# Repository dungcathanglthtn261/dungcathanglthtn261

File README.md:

# Smart Irrigation System – Bài tập lớn LTHTN (HK261)

Thiết bị đo độ ẩm đất và tự động tưới cây, dùng **STM32F103C8 (Blue Pill)** + FreeRTOS.
Đồ án môn **Lập trình Hệ thống nhúng** – HCMUT.

Nhóm: Dũng · Ca · Thắng

## Chức năng

- Đọc độ ẩm đất qua ADC mỗi 1000 ms, quy đổi 0–100 % (độ phân giải 1 %).
- **AUTO**: bật bơm khi độ ẩm < ngưỡng (setpoint), tắt khi đạt ngưỡng.
- **MANUAL**: bật/tắt bơm bằng nút PUMP, không phụ thuộc cảm biến.
- LCD 16x2 hiển thị độ ẩm, ngưỡng, chế độ, trạng thái bơm.
- Gửi dữ liệu lên PC qua UART, ví dụ: `SOIL: 45% | SET: 60% | MODE: AUTO | PUMP: ON`.

## Cấu trúc repo

```
docs/                Đề tài, yêu cầu chung, bảng phân công, sơ đồ khối
hardware/kicad/      Project KiCad: schematic, PCB 10x10 cm, thư viện symbol/footprint riêng
hardware/images/     Ảnh xem nhanh schematic và PCB
firmware/            Code STM32 + FreeRTOS: app/ (task, logic), middleware/ (soil_sensor, lcd16x02, relay_pump)
docs/test/           Kịch bản kiểm thử
docs/flowcharts/     Lưu đồ giải thuật (mermaid + png)
simulation/mokxi/    diagram.json (định dạng Wokwi) + sketch.ino để mô phỏng trên Mokxi/Wokwi
```

## Gán chân (Blue Pill)

| Khối | Chân | Ghi chú |
|---|---|---|
| Cảm biến độ ẩm | PA0 (ADC1_IN0) | Cấp 3V3, tụ lọc 100 nF |
| UART → PC | PA2 TX, PA3 RX (USART2) | 115200 8N1, nối chéo TX/RX với USB-UART |
| Relay | PA4 | Module relay 5V, kích mức **thấp** |
| LCD 16x2 (4-bit) | RS PB0, E PB1, D4–D7 PB10–PB13 | RW nối GND, biến trở 10k chỉnh tương phản, 220 Ω đèn nền |
| Nút MODE / UP / DOWN / PUMP | PB5 / PB6 / PB7 / PB8 | Pull-up nội, nhấn = LOW, tụ 100 nF chống dội |
| Nạp / debug | Header SWD trên Blue Pill | PA13/PA14 không có trên 2 hàng chân bên hông |

## Phần cứng (KiCad)

Mở `hardware/kicad/smart_irrigation.kicad_pro` bằng KiCad 9/10. Thư viện symbol và footprint
riêng đã khai báo trong `sym-lib-table` / `fp-lib-table` của project (đường dẫn `${KIPRJMOD}`).

- Board 100 × 100 mm, 2 lớp, mặt dưới phủ đồng GND, 4 lỗ M3.
- Blue Pill cắm qua 2 hàng **header cái 1x20** (hàng cách nhau 15.24 mm), không hàn trực tiếp.
- LCD cắm qua header cái 16 chân; relay module gắn ngoài (J7 điều khiển, J8 tiếp điểm COM/NO).
- Dây tín hiệu 0.5 mm, dây nguồn 1.0 mm, khoảng cách 0.3 mm.
- ERC: 0 lỗi. DRC: 0 lỗi, còn 4 cảnh báo silkscreen của footprint nút nhấn chuẩn KiCad.

**Cần kiểm tra trước khi đặt mạch:** in PCB tỉ lệ 1:1 để ướm Blue Pill thật (pinout, khoảng
cách hàng, chiều USB) và hướng lỗ luồn dây của cầu đấu vít.

## Mô phỏng

Ubuntu không chạy được Proteus, nhóm dùng **Mokxi** (mô phỏng trên trình duyệt):

- `simulation/mokxi/mokxi_project.json`: project định dạng Mokxi (`mokxi-ai/1`), đã qua
  `validate_project` của Mokxi, 0 lỗi. Dùng cảm biến độ ẩm điện dung, máy bơm mini chạy pin 4xAA
  qua relay kích mức thấp, diode chống dòng ngược. Serial Monitor in gói tin UART.
- **Project Mokxi (layout gọn, chạy được):** https://app.mokxi.com/p/RN2hMLpKIqXbyVL_  
  Vị trí/đường dây nằm trong `diagram_mokxi_native.json`; code Mokxi: `sketch_mokxi.ino`.
- `simulation/mokxi/diagram.json` + `sketch.ino`: bản định dạng Wokwi (biến trở thay cảm biến,
  LED thay máy bơm).

Hằng số `ADC_DRY` / `ADC_WET` trong code phải hiệu chuẩn lại trên mạch thật.

## Việc tiếp theo

- [ ] Firmware STM32CubeIDE + FreeRTOS (5 task: SensorRead, ButtonProcess, Control, Display, UART_Tx)
- [ ] Xuất Gerber, làm mạch, hàn linh kiện
- [ ] Hiệu chuẩn cảm biến, chạy kịch bản kiểm thử
- [ ] Báo cáo

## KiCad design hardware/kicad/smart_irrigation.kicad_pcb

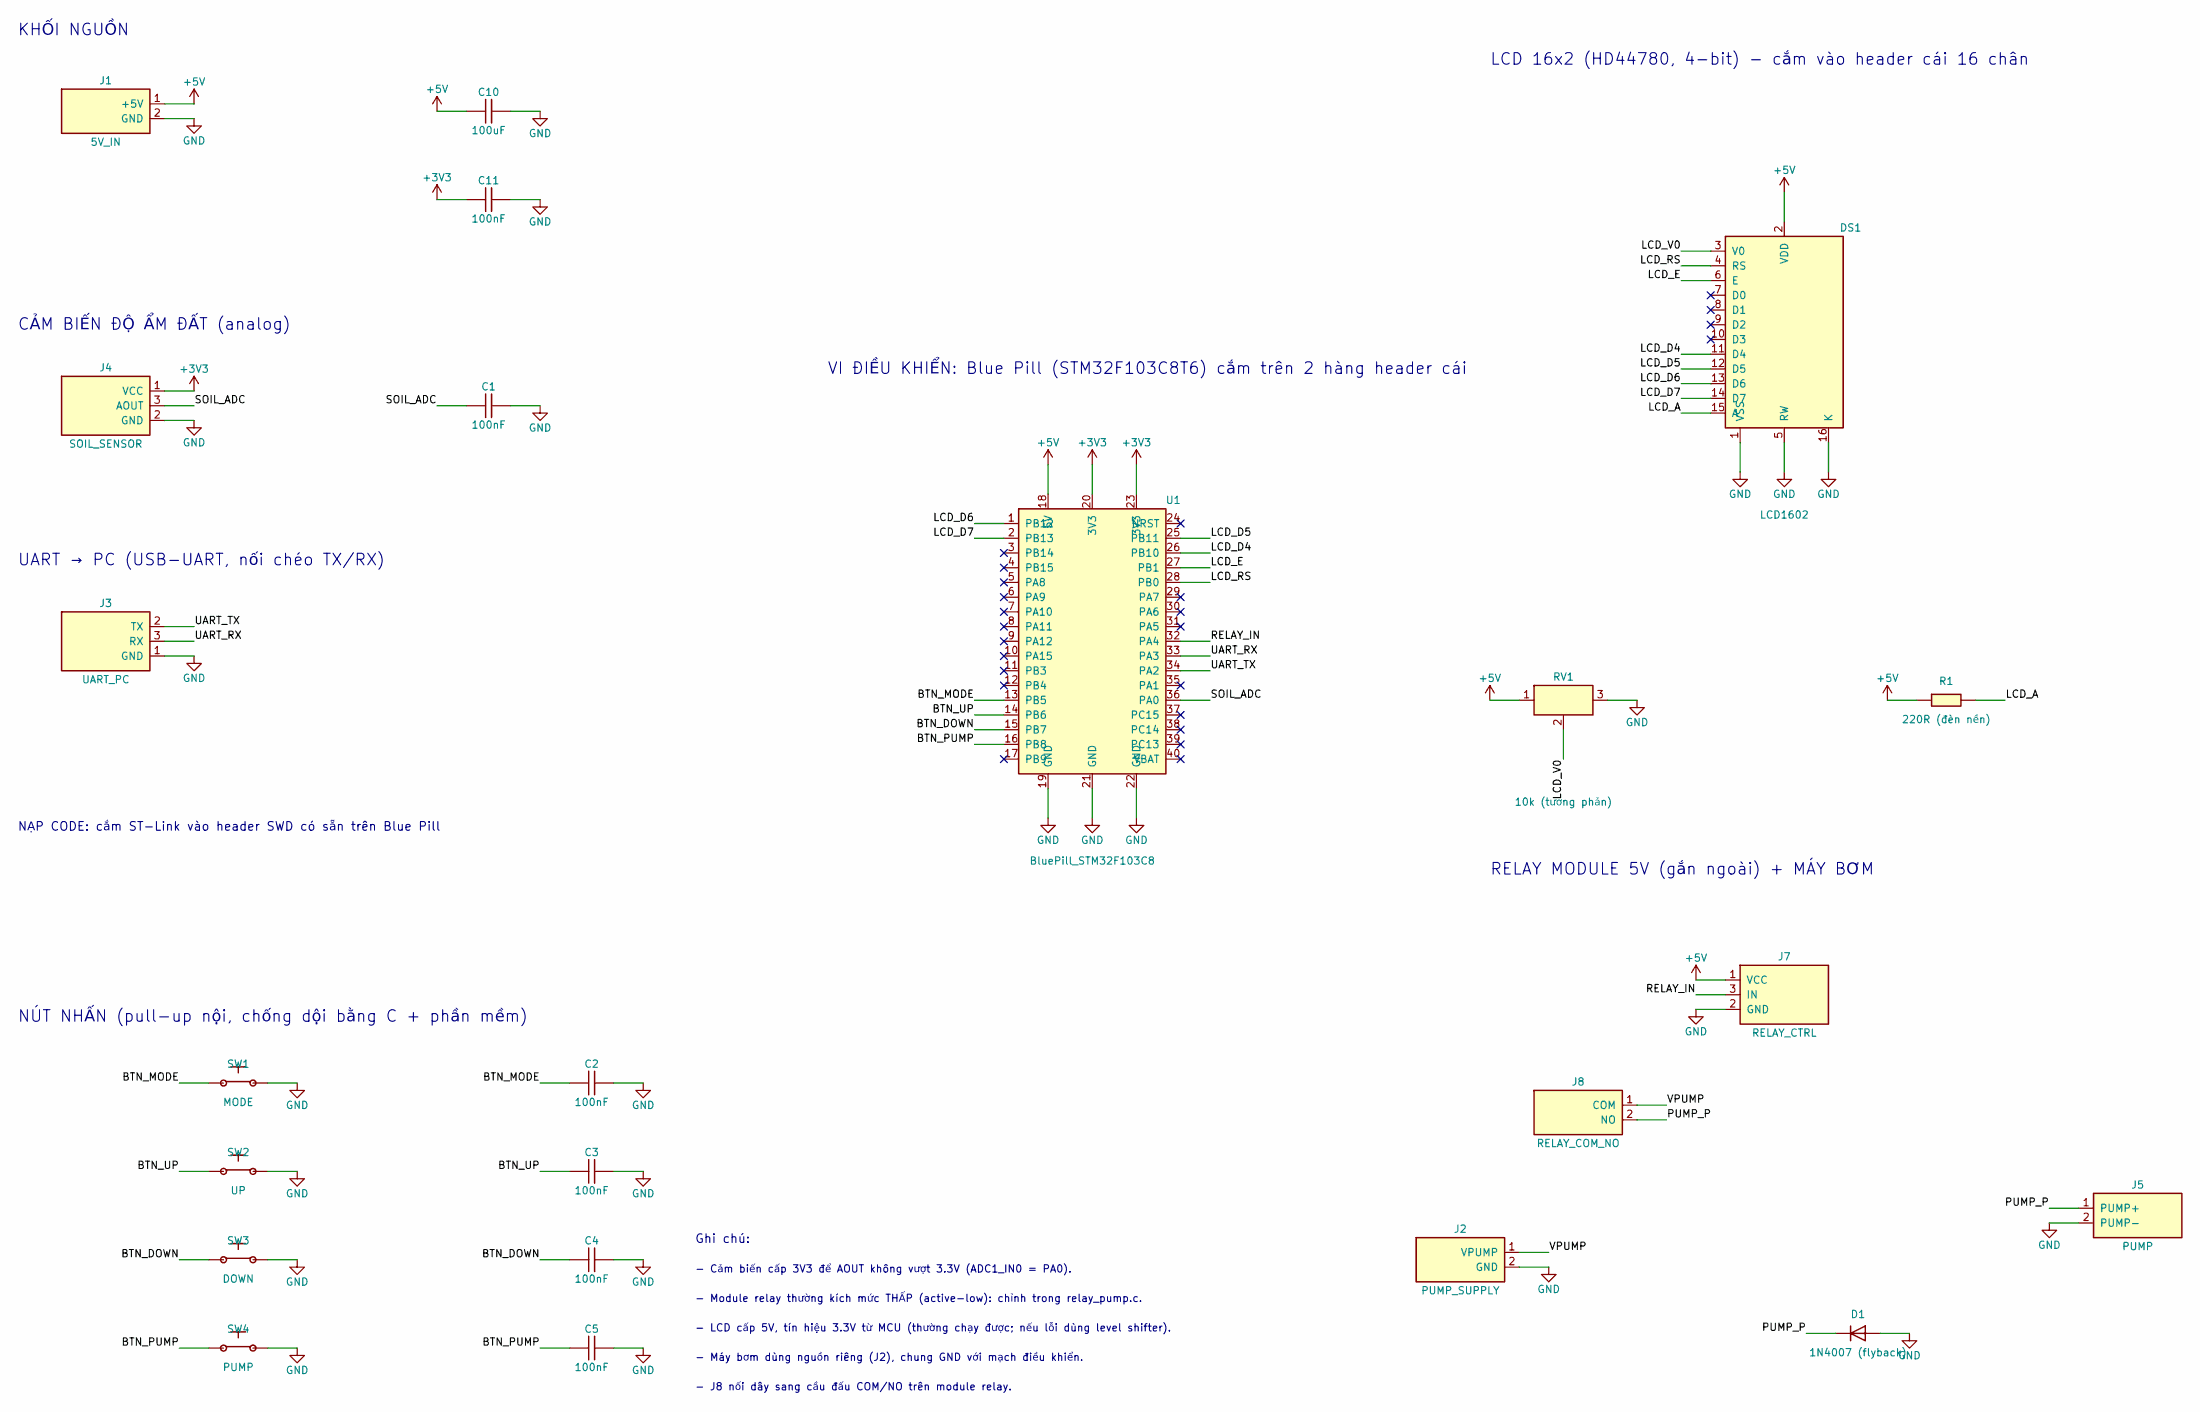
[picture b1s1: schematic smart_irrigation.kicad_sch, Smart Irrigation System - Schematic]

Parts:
C1, C2, C3, C4, C5, C11: 100nF; C_Disc_D5.0mm_W2.5mm_P5.00mm
C10: 100uF; CP_Radial_D6.3mm_P2.50mm
D1: 1N4007 (flyback); D_DO-41_SOD81_P10.16mm_Horizontal
DS1: LCD1602; PinSocket_1x16_P2.54mm_Vertical
J1: 5V_IN; TerminalBlock_Phoenix_MKDS-1,5-2_1x02_P5.00mm_Horizontal
J2: PUMP_SUPPLY; TerminalBlock_Phoenix_MKDS-1,5-2_1x02_P5.00mm_Horizontal
J3: UART_PC; PinHeader_1x03_P2.54mm_Vertical
J4: SOIL_SENSOR; PinHeader_1x03_P2.54mm_Vertical
J5: PUMP; TerminalBlock_Phoenix_MKDS-1,5-2_1x02_P5.00mm_Horizontal
J7: RELAY_CTRL; PinHeader_1x03_P2.54mm_Vertical
J8: RELAY_COM_NO; TerminalBlock_Phoenix_MKDS-1,5-2_1x02_P5.00mm_Horizontal
R1: 220R (đèn nền); R_Axial_DIN0207_L6.3mm_D2.5mm_P7.62mm_Horizontal
RV1: 10k (tương phản); Potentiometer_Bourns_3296W_Vertical
SW1: MODE; SW_PUSH_6mm
SW2: UP; SW_PUSH_6mm
SW3: DOWN; SW_PUSH_6mm
SW4: PUMP; SW_PUSH_6mm
U1: BluePill_STM32F103C8; BluePill_Socket

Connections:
+3V3: C11.1, J4.1 (VCC), U1.20 (3V3), U1.23 (3V3)
+5V: C10.1, DS1.2 (VDD), J1.1 (+5V), J7.1 (VCC), R1.1, RV1.1, U1.18 (5V)
BTN_DOWN: C4.1, SW3.1, U1.15 (PB7)
BTN_MODE: C2.1, SW1.1, U1.13 (PB5)
BTN_PUMP: C5.1, SW4.1, U1.16 (PB8)
BTN_UP: C3.1, SW2.1, U1.14 (PB6)
GND: C1.2, C2.2, C3.2, C4.2, C5.2, C10.2, C11.2, D1.2 (A), DS1.1 (VSS), DS1.5 (RW), DS1.16 (K), J1.2 (GND), J2.2 (GND), J3.1 (GND), J4.2 (GND), J5.2 (PUMP-), J7.2 (GND), RV1.3, SW1.2, SW2.2, SW3.2, SW4.2, U1.19 (GND), U1.21 (GND), U1.22 (GND)
LCD_A: DS1.15 (A), R1.2
LCD_D4: DS1.11 (D4), U1.26 (PB10)
LCD_D5: DS1.12 (D5), U1.25 (PB11)
LCD_D6: DS1.13 (D6), U1.1 (PB12)
LCD_D7: DS1.14 (D7), U1.2 (PB13)
LCD_E: DS1.6 (E), U1.27 (PB1)
LCD_RS: DS1.4 (RS), U1.28 (PB0)
LCD_V0: DS1.3 (V0), RV1.2 (W)
PUMP_P: D1.1 (K), J5.1 (PUMP+), J8.2 (NO)
RELAY_IN: J7.3 (IN), U1.32 (PA4)
SOIL_ADC: C1.1, J4.3 (AOUT), U1.36 (PA0)
UART_RX: J3.3 (RX), U1.33 (PA3)
UART_TX: J3.2 (TX), U1.34 (PA2)
VPUMP: J2.1 (VPUMP), J8.1 (COM)

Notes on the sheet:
KHỐI NGUỒN
CẢM BIẾN ĐỘ ẨM ĐẤT (analog)
UART → PC (USB-UART, nối chéo TX/RX)
NẠP CODE: cắm ST-Link vào header SWD có sẵn trên Blue Pill
NÚT NHẤN (pull-up nội, chống dội bằng C + phần mềm)
VI ĐIỀU KHIỂN: Blue Pill (STM32F103C8T6) cắm trên 2 hàng header cái
LCD 16x2 (HD44780, 4-bit) - cắm vào header cái 16 chân
RELAY MODULE 5V (gắn ngoài) + MÁY BƠM
Ghi chú:
- Cảm biến cấp 3V3 để AOUT không vượt 3.3V (ADC1_IN0 = PA0).
- Module relay thường kích mức THẤP (active-low): chỉnh trong relay_pump.c.
- LCD cấp 5V, tín hiệu 3.3V từ MCU (thường chạy được; nếu lỗi dùng level shifter).
- Máy bơm dùng nguồn riêng (J2), chung GND với mạch điều khiển.
- J8 nối dây sang cầu đấu COM/NO trên module relay.

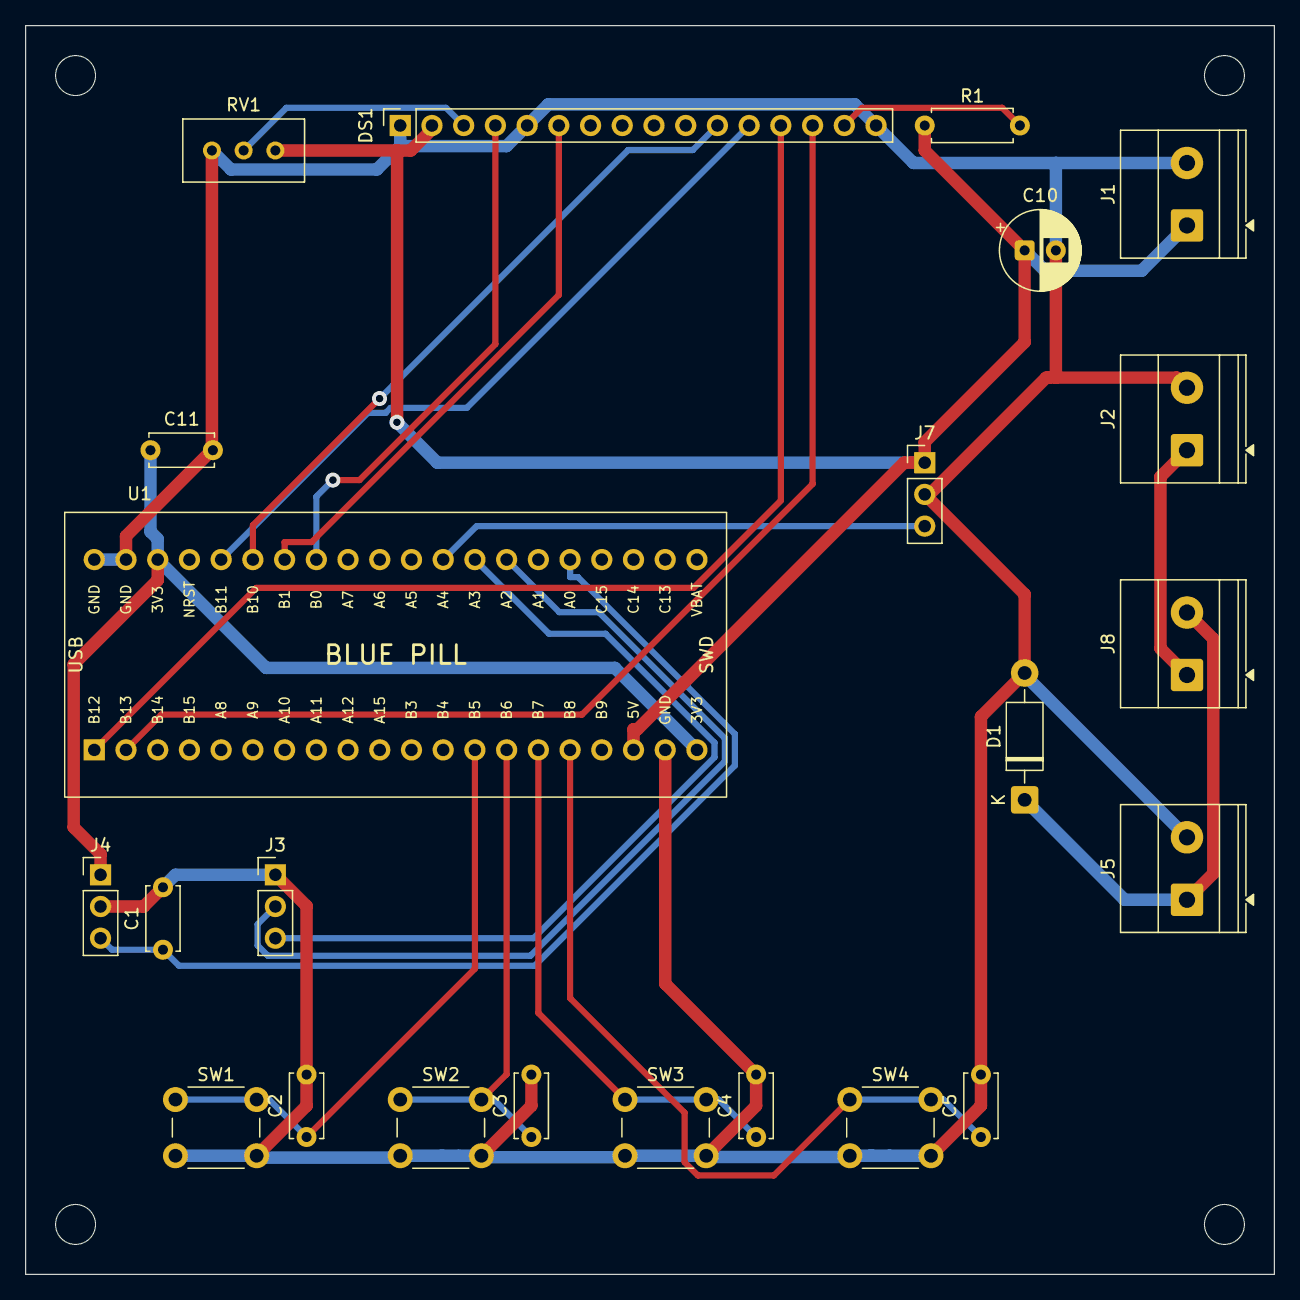
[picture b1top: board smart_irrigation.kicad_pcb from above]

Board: 2 copper layers, 100.0 x 100.0 mm, 27 parts (0 on the bottom side), 21 nets.

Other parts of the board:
MH1, MH2, MH3, MH4: M3; MountingHole_3.2mm_M3

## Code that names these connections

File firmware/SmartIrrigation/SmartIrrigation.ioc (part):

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Mcu.Name=STM32F103C(8-B)Tx
Mcu.Package=LQFP48
Mcu.UserName=STM32F103C8Tx
PA0-WKUP.Signal=ADCx_IN0
PA13.Mode=Serial_Wire
PA13.Signal=SYS_JTMS-SWDIO
PA14.Mode=Serial_Wire
PA14.Signal=SYS_JTCK-SWCLK
PA2.Mode=Asynchronous
PA2.Signal=USART2_TX
PA3.Mode=Asynchronous
PA3.Signal=USART2_RX
PA4.GPIOParameters=PinState,GPIO_Label
PA4.GPIO_Label=RELAY
PA4.PinState=GPIO_PIN_SET
PA4.Signal=GPIO_Output
PB0.GPIOParameters=GPIO_Label
PB0.GPIO_Label=LCD_RS
PB0.Signal=GPIO_Output
PB1.GPIOParameters=GPIO_Label
PB1.GPIO_Label=LCD_EN
PB1.Signal=GPIO_Output
PB10.GPIOParameters=GPIO_Label
PB10.GPIO_Label=LCD_D4
PB10.Signal=GPIO_Output
PB11.GPIOParameters=GPIO_Label
PB11.GPIO_Label=LCD_D5
PB11.Signal=GPIO_Output
PB12.GPIOParameters=GPIO_Label
PB12.GPIO_Label=LCD_D6
PB12.Signal=GPIO_Output
PB13.GPIOParameters=GPIO_Label
PB13.GPIO_Label=LCD_D7
PB13.Signal=GPIO_Output
PB5.GPIOParameters=GPIO_PuPd,GPIO_Label
PB5.GPIO_Label=BTN_MODE
PB5.GPIO_PuPd=GPIO_PULLUP
PB5.Signal=GPIO_Input
PB6.GPIOParameters=GPIO_PuPd,GPIO_Label
PB6.GPIO_Label=BTN_UP
PB6.GPIO_PuPd=GPIO_PULLUP
PB6.Signal=GPIO_Input
PB7.GPIOParameters=GPIO_PuPd,GPIO_Label
PB7.GPIO_Label=BTN_DOWN
PB7.GPIO_PuPd=GPIO_PULLUP
PB7.Signal=GPIO_Input
PB8.GPIOParameters=GPIO_PuPd,GPIO_Label
PB8.GPIO_Label=BTN_PUMP
PB8.GPIO_PuPd=GPIO_PULLUP
PB8.Signal=GPIO_Input
PD0-OSC_IN.Mode=HSE-External-Oscillator
PD0-OSC_IN.Signal=RCC_OSC_IN
PD1-OSC_OUT.Mode=HSE-External-Oscillator
PD1-OSC_OUT.Signal=RCC_OSC_OUT
RCC.SYSCLKFreq_VALUE=72000000
RCC.SYSCLKSource=RCC_SYSCLKSOURCE_PLLCLK
board=custom
